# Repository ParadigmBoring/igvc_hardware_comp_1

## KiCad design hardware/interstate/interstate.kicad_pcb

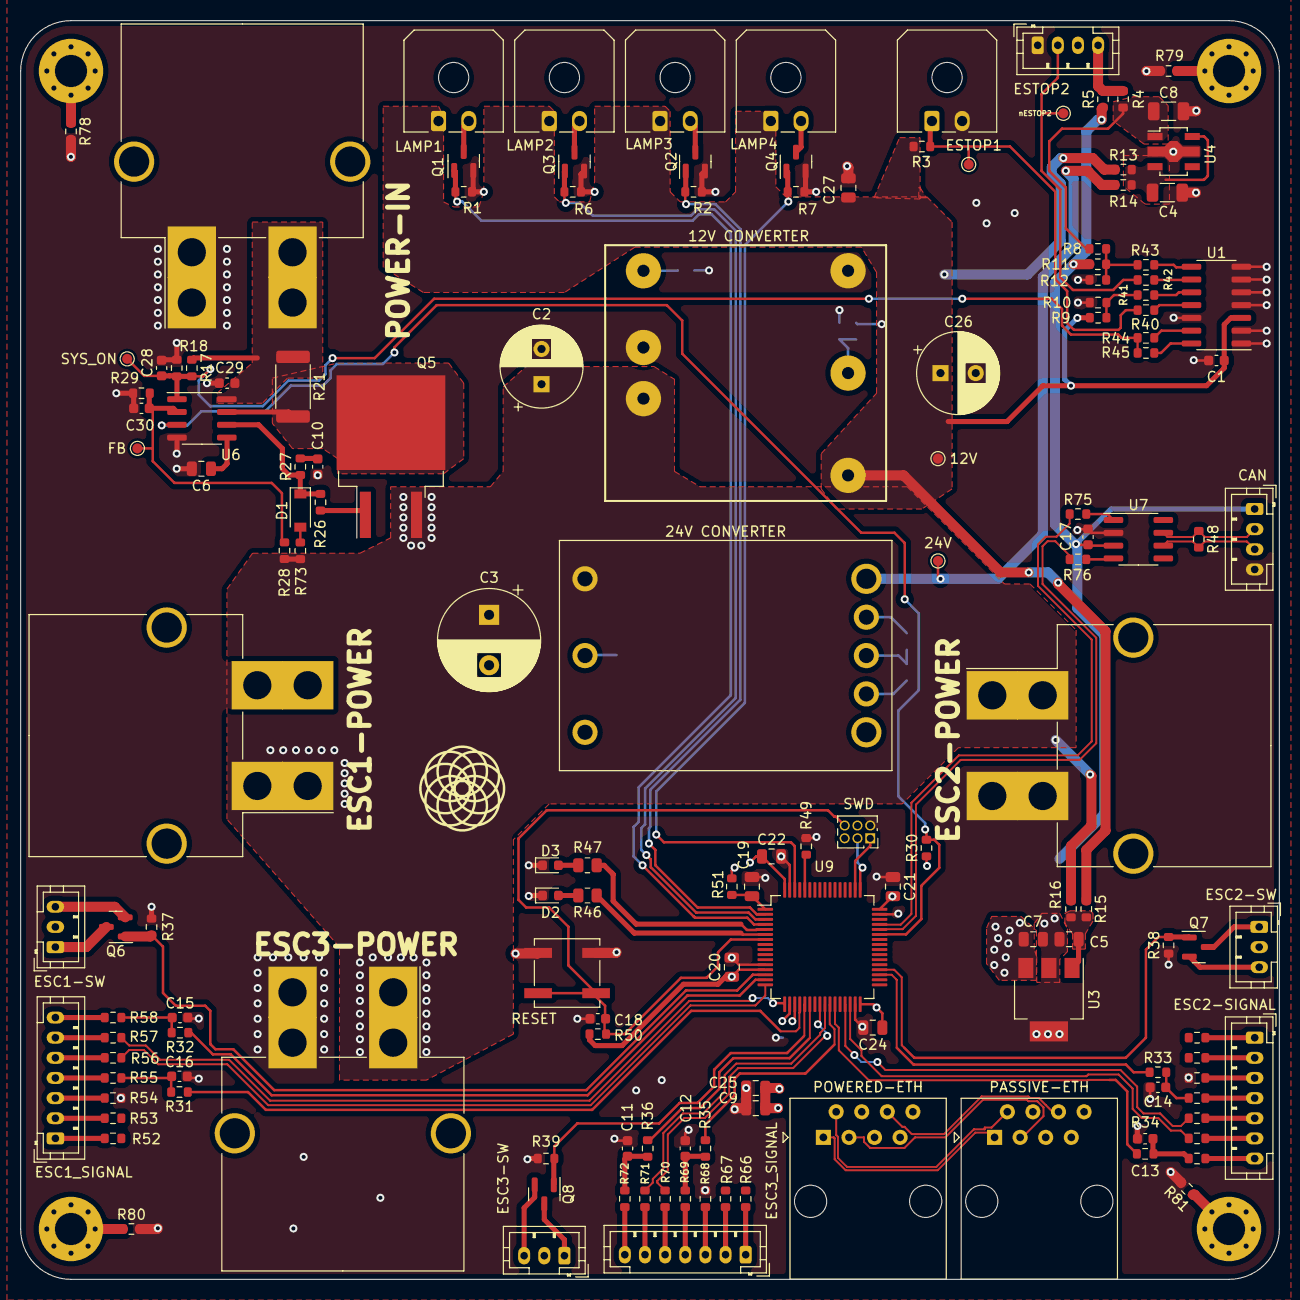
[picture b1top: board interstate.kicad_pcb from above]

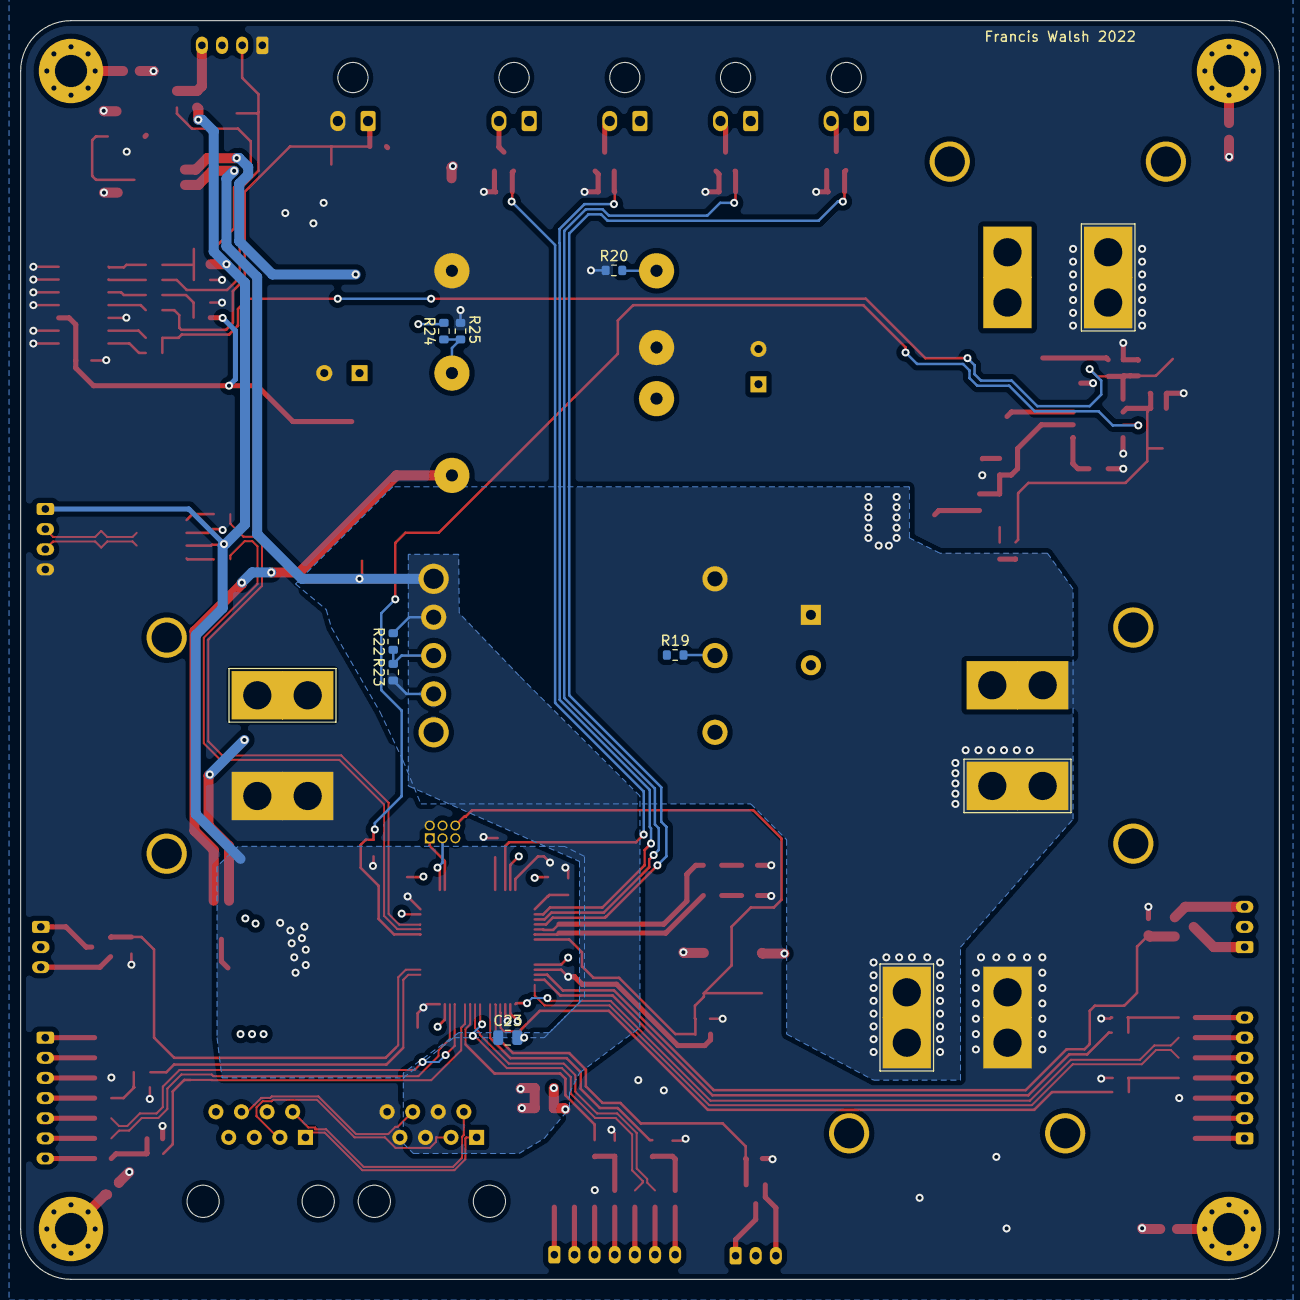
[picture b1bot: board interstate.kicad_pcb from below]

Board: 4 copper layers, 125.0 x 125.0 mm, 158 parts (7 on the bottom side), 112 nets.

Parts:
12V, 24V: TestPoint_Pad_D1.0mm
12V CONVERTER: SHHD001A3B41Z; SHHD001A3B
24V CONVERTER: VCB4824SBO; VCB4824SB0-30WR3
C1, C11, C12, C13, C14, C15, C16, C17, C18, C28, C29, C30: 10nF; C_0603_1608Metric
C2, C26: 33uF; CP_Radial_D8.0mm_P3.50mm
C3: 100uF; CP_Radial_D10.0mm_P5.00mm
C4, C8: 1uF; C_1206_3216Metric
C5, C7: 2.2uF; C_0805_2012Metric
C6: ??nF; C_0805_2012Metric
C9, C25: 4.7uF; C_0805_2012Metric
C10: ??nF; C_0603_1608Metric
C19, C20, C21, C22, C23, C24, C27: 0.1uF; C_0805_2012Metric
CAN: CAN; JST_PH_B4B-PH-K_1x04_P2.00mm_Vertical
D1: PN; D_SOD-123
D2, D3: RED; LED_0603_1608Metric
ESC1-POWER: ESC1_PWR; Molex_Mini-Fit_Sr_42820-22XX_1x02_P10.00mm_Horizontal
ESC1-SW: ESC1_SW; JST_PH_B3B-PH-K_1x03_P2.00mm_Vertical
ESC1_SIGNAL: ESC1_CTRL; JST_PH_B7B-PH-K_1x07_P2.00mm_Vertical
ESC2-POWER: ESC3_PWR; Molex_Mini-Fit_Sr_42820-22XX_1x02_P10.00mm_Horizontal
ESC2-SIGNAL: ESC2_CTRL; JST_PH_B7B-PH-K_1x07_P2.00mm_Vertical
ESC2-SW: ESC2_SW; JST_PH_B3B-PH-K_1x03_P2.00mm_Vertical
ESC3-POWER: ESC2_PWR; Molex_Mini-Fit_Sr_42820-22XX_1x02_P10.00mm_Horizontal
ESC3-SW: ESC3_SW; JST_PH_B3B-PH-K_1x03_P2.00mm_Vertical
ESC3_SIGNAL: ESC3_CTRL; JST_PH_B7B-PH-K_1x07_P2.00mm_Vertical
ESTOP1: ESTOP1; Molex_Micro-Fit_3.0_43650-0200_1x02_P3.00mm_Horizontal
ESTOP2: ESTOP2; JST_PH_B4B-PH-K_1x04_P2.00mm_Vertical
FB: TestPoint_Pad_D1.0mm
H1, H2, H3, H4: M3; MountingHole_3.2mm_M3_Pad_Via
LAMP1: Lamp 1 Out; Molex_Micro-Fit_3.0_43650-0200_1x02_P3.00mm_Horizontal
LAMP2: Lamp 2 Out; Molex_Micro-Fit_3.0_43650-0200_1x02_P3.00mm_Horizontal
LAMP3: Lamp 3 Out; Molex_Micro-Fit_3.0_43650-0200_1x02_P3.00mm_Horizontal
LAMP4: Lamp 4 Out; Molex_Micro-Fit_3.0_43650-0200_1x02_P3.00mm_Horizontal
PASSIVE-ETH: RJ45; RJ45_Amphenol_54602-x08_Horizontal
POWER-IN: Conn_01x02; Molex_Mini-Fit_Sr_42820-22XX_1x02_P10.00mm_Horizontal
POWERED-ETH: RJ45; RJ45_Amphenol_54602-x08_Horizontal
Q1, Q2, Q3, Q4, Q6, Q7, Q8: 2N7002; SOT-23
Q5: Q_NMOS_GDS; TO-263-2
R1, R2, R3, R6, R7, R8, R9, R10, R11, R12, R30, R31, R32, R33, R34, R35, R36, R37, R38, R39, R49, R50, R73: 1k; R_0603_1608Metric
R4, R5, R13, R14, R15, R16, R19, R20, R40, R41, R42, R43, R44, R45, R51, R52, R53, R54, R55, R56, R57, R58, R59, R60, R61, R62, R63, R64, R65, R66, R67, R68, R69, R70, R71, R72, R75, R76, R78, R79, R80, R81: 0; R_0603_1608Metric
R17, R18, R27, R28, R29: ???; R_0603_1608Metric
R21: 1; R_2512_6332Metric
R22, R23, R24, R25: 10k; R_0603_1608Metric
R26: 10; R_0603_1608Metric
R46, R47: 330; R_0805_2012Metric
R48: 120; R_0603_1608Metric
RESET: RST; SW_SPST_B3SL-1022P
SWD: SWD; PinSocket_2x03_P1.27mm_Vertical
SYS_ON: TestPoint_Pad_D1.0mm
U1: LM339; SOIC-14_3.9x8.7mm_P1.27mm
U3: MCP1792T; SOT-223
U4: MCP1804x-3302xMT; SOT-89-5
U6: LT1641-1; SOIC-8_3.9x4.9mm_P1.27mm
U7: SN65HVD232; SOIC-8_3.9x4.9mm_P1.27mm
U9: STM32F334R8Tx; LQFP-64_10x10mm_P0.5mm
nESTOP2: TestPoint_Pad_D1.0mm

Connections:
+3V3: C7.2, C17.1, C20.1, C21.1, C22.1, C23.1, C24.1, CAN.1, R5.1, R11.1, R30.1, R50.1, R51.2, U3.3 (VOUT), U7.3 (VCC), U9.13 (VDDA), U9.19 (VDD), U9.32 (VDD), U9.48 (VDD), U9.64 (VDD)
+5V: C8.1, R4.1, R8.1, U4.1 (VOUT)
+12V: 12V.1, 12V CONVERTER.6 (VOUT+), C1.2, C26.1, C27.1, LAMP1.1, LAMP2.1, LAMP3.1, LAMP4.1, R3.1, R9.1, R13.1, R15.1, R24.2, U1.3 (V+)
+24V: 24V.1, 24V CONVERTER.7 (SENSE+), 24V CONVERTER.8 (+VO), C9.2, C25.2, POWERED-ETH.4, POWERED-ETH.5, R14.1, R22.2
/BATT_GOOD: R30.2, U6.3 (PWRGD), U9.43 (PA10)
/BATT_PROT: 12V CONVERTER.1 (VIN+), 24V CONVERTER.1 (VIN), C2.1, C3.1, ESC1-POWER.1, ESC2-POWER.1, ESC3-POWER.1, Q5.3 (S), R16.1, R28.1, R73.1
/BATT_RAW: C29.1, POWER-IN.2, R17.1, R21.1, U6.8 (VCC)
/CAN+: CAN.2, R48.1, U7.7 (CANH)
/CAN-: CAN.3, R48.2, U7.6 (CANL)
/CAN_N: R76.1, U9.44 (PA11)
/CAN_P: R75.1, U9.45 (PA12)
/ESC1_ADC1: C16.1, R31.2, R55.1
/ESC1_ADC1_UNFILT: R31.1, U9.20 (PA4)
/ESC1_ADC2: C15.1, R32.2, R58.1
/ESC1_ADC2_UNFILT: R32.1, U9.15 (PA1)
/ESC1_N: R57.1, U9.17 (PA3)
/ESC1_ON: Q6.1 (G), R37.1, U9.14 (PA0)
/ESC1_P: R56.1, U9.16 (PA2)
/ESC1_SW1: ESC1-SW.1, Q6.3 (D)
/ESC1_SW2: ESC1-SW.3, Q6.2 (S)
/ESC2_ADC1: C14.1, R33.2, R62.1
/ESC2_ADC1_UNFILT: R33.1, U9.35 (PB14)
/ESC2_ADC2: C13.1, R34.2, R65.1
/ESC2_ADC2_UNFILT: R34.1, U9.27 (PB1)
/ESC2_N: R64.1, U9.30 (PB11)
/ESC2_ON: Q7.1 (G), R38.1, U9.36 (PB15)
/ESC2_P: R63.1, U9.29 (PB10)
/ESC2_SW1: ESC2-SW.1, Q7.3 (D)
/ESC2_SW2: ESC2-SW.3, Q7.2 (S)
/ESC3_ADC1: C12.1, R35.2, R69.1
/ESC3_ADC1_UNFILT: R35.1, U9.26 (PB0)
/ESC3_ADC2: C11.1, R36.2, R72.1
/ESC3_ADC2_UNFILT: R36.1, U9.22 (PA6)
/ESC3_N: R71.1, U9.25 (PC5)
/ESC3_ON: Q8.1 (G), R39.1, U9.21 (PA5)
/ESC3_P: R70.1, U9.24 (PC4)
/ESC3_SW1: ESC3-SW.1, Q8.3 (D)
/ESC3_SW2: ESC3-SW.3, Q8.2 (S)
/LAMP1_ON: Q1.1 (G), R1.1, U9.4 (PC15)
/LAMP2_ON: Q3.1 (G), R6.1, U9.3 (PC14)
/LAMP3_ON: Q2.1 (G), R2.1, U9.2 (PC13)
/LAMP4_ON: Q4.1 (G), R7.1, U9.62 (PB9)
/LED1: R47.1, U9.5 (PF0)
/LED2: R46.1, U9.6 (PF1)
/RX_N: PASSIVE-ETH.2, POWERED-ETH.2
/RX_P: PASSIVE-ETH.1, POWERED-ETH.1
/SWCLK: SWD.3, U9.49 (PA14)
/SWDIO: SWD.1, U9.50 (PA15)
/SYS_ON: C28.1, R17.2, R18.1, R44.2, R45.2, SYS_ON.1, U6.1 (ON)
/TX_N: PASSIVE-ETH.6, POWERED-ETH.6
/TX_P: PASSIVE-ETH.3, POWERED-ETH.3
/VBAT: C19.1, R51.1, U9.1 (VBAT)
/nESTOP1: ESTOP1.1, R3.2, R40.1
/nESTOP2: ESTOP2.2, R42.1, nESTOP2.1
/nRESET: C18.1, R50.2, RESET.2 (B), SWD.6, U9.7 (NRST)
GND: 12V CONVERTER.2 (VIN-), 12V CONVERTER.4 (VOUT-), 24V CONVERTER.3 (GND), 24V CONVERTER.4 (0V), 24V CONVERTER.5 (SENSE-), C1.1, C2.2, C3.2, C4.2, C5.1, C6.2, C7.1, C8.2, C9.1, C10.2, C11.2, C12.2, C13.2, C14.2, C15.2, C16.2, C17.2, C18.2, C19.2, C20.2, C21.2, C22.2, C23.2, C24.2, C25.1, C26.2, C27.2, C28.2, C29.2, C30.2, CAN.4, D2.1 (K), D3.1 (K), ESC1-POWER.2, ESC2-POWER.2, ESC3-POWER.2, ESTOP1.2, ESTOP2.1, POWER-IN.1, POWERED-ETH.7, POWERED-ETH.8, Q1.2 (S), Q2.2 (S), Q3.2 (S), Q4.2 (S), R1.2, R2.2, R6.2, R7.2, R10.2, R12.2, R18.2, R20.1, R23.1, R25.1, R29.2, R37.2, R38.2, R39.2, R49.2, R54.1, R61.1, R68.1, R78.2, R79.2, R80.2, R81.2, RESET.1 (A), SWD.2, U1.1, U1.2, U1.4 (-), U1.5 (+), U1.6 (-), U1.7 (+), U1.12 (V-), U3.2 (GND), U3.4 (GND), U4.2 (GND), U6.4 (GND), U7.2 (GND), U9.12 (VSSA), U9.18 (VSS), U9.31 (VSS), U9.47 (VSS), U9.63 (VSS)
unnamed: C4.1, R13.2, R14.2, U4.3 (~SHDN), U4.5 (VIN)
unnamed: C5.2, R15.2, R16.2, U3.1 (VIN)
unnamed: C6.1, U6.5 (TIMER)
unnamed: C10.1, R27.2
unnamed: C30.1, FB.1, R28.2, R29.1, U6.2 (FB)
unnamed: D1.1 (K), R26.1, R27.1, U6.6 (GATE)
unnamed: D1.2 (A), R73.2
unnamed: D2.2 (A), R46.2
unnamed: D3.2 (A), R47.2
unnamed: H1.1, R78.1
unnamed: H2.1, R79.1
unnamed: H3.1, R80.1
unnamed: H4.1, R81.1
unnamed: LAMP1.2, Q1.3 (D)
unnamed: LAMP3.2, Q2.3 (D)
unnamed: LAMP2.2, Q3.3 (D)
unnamed: LAMP4.2, Q4.3 (D)
unnamed: ESC1_SIGNAL.1, R52.2
unnamed: ESC1_SIGNAL.2, R53.2
unnamed: ESC1_SIGNAL.3, R54.2
unnamed: ESC1_SIGNAL.4, R55.2
unnamed: ESC1_SIGNAL.5, R56.2
unnamed: ESC1_SIGNAL.6, R57.2
unnamed: ESC1_SIGNAL.7, R58.2
unnamed: ESC2-SIGNAL.1, R59.2
unnamed: ESC2-SIGNAL.2, R60.2
unnamed: ESC2-SIGNAL.3, R61.2
unnamed: ESC2-SIGNAL.4, R62.2
unnamed: ESC2-SIGNAL.5, R63.2
unnamed: ESC2-SIGNAL.6, R64.2
unnamed: ESC2-SIGNAL.7, R65.2
unnamed: ESC3_SIGNAL.1, R66.2
unnamed: ESC3_SIGNAL.2, R67.2
unnamed: ESC3_SIGNAL.3, R68.2
unnamed: ESC3_SIGNAL.4, R69.2
unnamed: ESC3_SIGNAL.5, R70.2
unnamed: ESC3_SIGNAL.6, R71.2
unnamed: ESC3_SIGNAL.7, R72.2
unnamed: Q5.1 (G), R26.2
unnamed: Q5.2 (D), R21.2, U6.7 (SENSE)
unnamed: ESTOP2.4, R4.2, R5.2
unnamed: R9.2, R10.1, R41.1
unnamed: R8.2, R11.2, R12.1, R43.1
unnamed: 24V CONVERTER.2 (CTRL), R19.2
unnamed: 12V CONVERTER.3 (ON/OFF), R20.2
unnamed: 24V CONVERTER.6 (TRIM), R22.1, R23.2
unnamed: 12V CONVERTER.5 (TRIM), R24.1, R25.2
unnamed: R40.2, U1.11 (+)
unnamed: R41.2, U1.10 (-)
unnamed: R42.2, U1.9 (+)
unnamed: R43.2, U1.8 (-)
unnamed: R44.1, U1.13
unnamed: R45.1, U1.14
unnamed: R49.1, U9.60 (BOOT0)
unnamed: R75.2, U7.1 (D)
unnamed: R76.2, U7.4 (R)

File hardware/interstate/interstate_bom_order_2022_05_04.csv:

Item,Qty,Reference(s),Value,Digikey,Power,Voltage
1,25,"C1, C11, C12, C13, C14, C15, C16, C17, C18, C28, C29, C30",10nF,445-1305-1-ND,,25V
2,10,"C2, C26",33uF,1189-2152-ND,,
3,10,C3,100uF,1189-1887-ND,,
4,10,"C4, C8",1uF,1276-1838-1-ND,,
5,10,"C5, C7",2.2uF,490-GRM21BD72A225KE01LCT-ND,,75V
6,10,C6,64nF,1292-1462-1-ND,,
7,10,"C9, C25",4.7uF,478-08055C225KAT2ACT-ND,,50V
9,20,"C19, C20, C21, C22, C23, C24, C27",0.1uF,1276-1099-1-ND,,
10,3,D1,PN,3757-BZT52-C10_R1_00001CT-ND,,
11,5,"D2, D3",RED,160-1445-1-ND,,
13,12,J1,Lamp 1 Out,WM1865-ND,,
19,10,J7,Conn_01x02,0428202224-ND,,
20,5,"J8, J9",RJ45,609-1046-ND,,
31,3,J20,SWD,S9015E-03-ND,,
33,10,"Q1, Q2, Q3, Q4, Q6, Q7, Q8",2N7002,2N7002A-7DICT-ND,,
34,2,Q5,Q_NMOS_GDS,1727-1890-1-ND,,
35,50,"R1, R2, R3, R6, R7, R8, R9, R10, R11, R12, R30, R31, R32, R33, R34, R35, R36, R37, R38, R39, R49, R50, R73",1k,RMCF0603FT1K00CT-ND,,
36,100,"R4, R5, R13, R14, R15, R16, R19, R20, R40, R41, R42, R43, R44, R45, R51, R52, R53, R54, R55, R56, R57, R58, R59, R60, R61, R62, R63, R64, R65, R66, R67, R68, R69, R70, R71, R72, R75, R76, R78, R79, R80, R81",0,RMCF0603ZT0R00CT-ND,,
37,10,"R17, R28",50k,A102282CT-ND,50mW,
38,10,"R18, R29",1.35k,13-RT0603BRD071K35LCT-ND,1mW,
39,10,R21,1,A131795CT-ND,1W,
41,10,R26,10,RMCF0603FT10R0CT-ND,,
43,10,"R46, R47",330,RHM330KCT-ND,,
44,10,R48,120,A129677CT-ND,,
45,3,SW1,RST,SW1104CT-ND,,
46,3,SW2,SW_SPDT,EG1903-ND,,
50,3,U4,MCP1804x-3302xMT,MCP1804T-5002I/MTCT-ND,,
51,20,,Molex 2 pin mate,WM1845-ND,,
52,20,,Molex pre crimped wires,0430300001-12-B0-ND,,
53,3,,Big Molex Cable Assemblies,900-0369240203-ND,,
54,2,,SWD cable assembly,SAM8668-ND,,

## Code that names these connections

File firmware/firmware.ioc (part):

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Mcu.Name=STM32F334R(6-8)Tx
Mcu.Package=LQFP64
Mcu.UserName=STM32F334R8Tx
PA0.GPIOParameters=GPIO_Label
PA0.GPIO_Label=ESC1_ON
PA0.Signal=GPIO_Output
PA1.GPIOParameters=GPIO_Label
PA1.GPIO_Label=ESC1_ADC2_UNFILT
PA1.Signal=S_TIM2_CH2
PA10.GPIOParameters=GPIO_Label
PA10.GPIO_Label=BATT_GOOD
PA10.Signal=GPIO_Input
PA11.Mode=CAN_Activate
PA11.Signal=CAN_RX
PA12.Mode=CAN_Activate
PA12.Signal=CAN_TX
PA13.Mode=Serial_Wire
PA13.Signal=SYS_JTMS-SWDIO
PA14.Mode=Serial_Wire
PA14.Signal=SYS_JTCK-SWCLK
PA15.Mode=I2C
PA15.Signal=I2C1_SCL
PA2.GPIOParameters=GPIO_Label
PA2.GPIO_Label=ESC1_TX
PA2.Mode=Asynchronous
PA2.Signal=USART2_TX
PA3.GPIOParameters=GPIO_Label
PA3.GPIO_Label=ESC1_RX
PA3.Mode=Asynchronous
PA3.Signal=USART2_RX
PA4.Signal=S_TIM3_CH2
PA5.Signal=GPIO_Output
PA6.Signal=S_TIM3_CH1
PA7.Mode=Full_Duplex_Master
PA7.Signal=SPI1_MOSI
PB0.Signal=S_TIM3_CH3
PB1.Signal=GPIO_Output
PB10.Mode=Asynchronous
PB10.Signal=USART3_TX
PB11.Mode=Asynchronous
PB11.Signal=USART3_RX
PB13.Signal=GPIO_Output
PB14.Signal=S_TIM15_CH1
PB15.Signal=S_TIM15_CH2
PB3.Mode=Full_Duplex_Master
PB3.Signal=SPI1_SCK
PB4.Mode=Full_Duplex_Master
PB4.Signal=SPI1_MISO
PB5.Signal=GPIO_Output
PB7.Mode=I2C
PB7.Signal=I2C1_SDA
PB9.GPIOParameters=GPIO_Label
PB9.GPIO_Label=LAMP4_ON
PB9.Signal=GPIO_Output
PC13.GPIOParameters=GPIO_Label
PC13.GPIO_Label=LAMP3_ON
PC13.Signal=GPIO_Output
PC14\ /\ OSC32_IN.GPIOParameters=GPIO_Label
PC14\ /\ OSC32_IN.GPIO_Label=LAMP2_ON
PC14\ /\ OSC32_IN.Signal=GPIO_Output
PC15\ /\ OSC32_OUT.GPIOParameters=GPIO_Label
PC15\ /\ OSC32_OUT.GPIO_Label=LAMP1_ON
PC15\ /\ OSC32_OUT.Signal=GPIO_Output
PC4.Mode=Asynchronous
PC4.Signal=USART1_TX
PC5.Mode=Asynchronous
PC5.Signal=USART1_RX
PF0\ /\ OSC_IN.GPIOParameters=GPIO_Label
PF0\ /\ OSC_IN.GPIO_Label=LED1
PF0\ /\ OSC_IN.Signal=GPIO_Output
PF1\ /\ OSC_OUT.GPIOParameters=GPIO_Label
PF1\ /\ OSC_OUT.GPIO_Label=LED2
PF1\ /\ OSC_OUT.Signal=GPIO_Output
RCC.HSEPLLFreq_Value=8000000
RCC.HSE_VALUE=8000000
RCC.SYSCLKFreq_VALUE=8000000
board=custom

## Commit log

2022-04-29 First commit - layout attempt 1
2022-04-29 routing first try
2022-05-02 More routing work - changed some MCU pinout
2022-05-03 finished routing v1?
2022-05-04 ordered board + BOM
